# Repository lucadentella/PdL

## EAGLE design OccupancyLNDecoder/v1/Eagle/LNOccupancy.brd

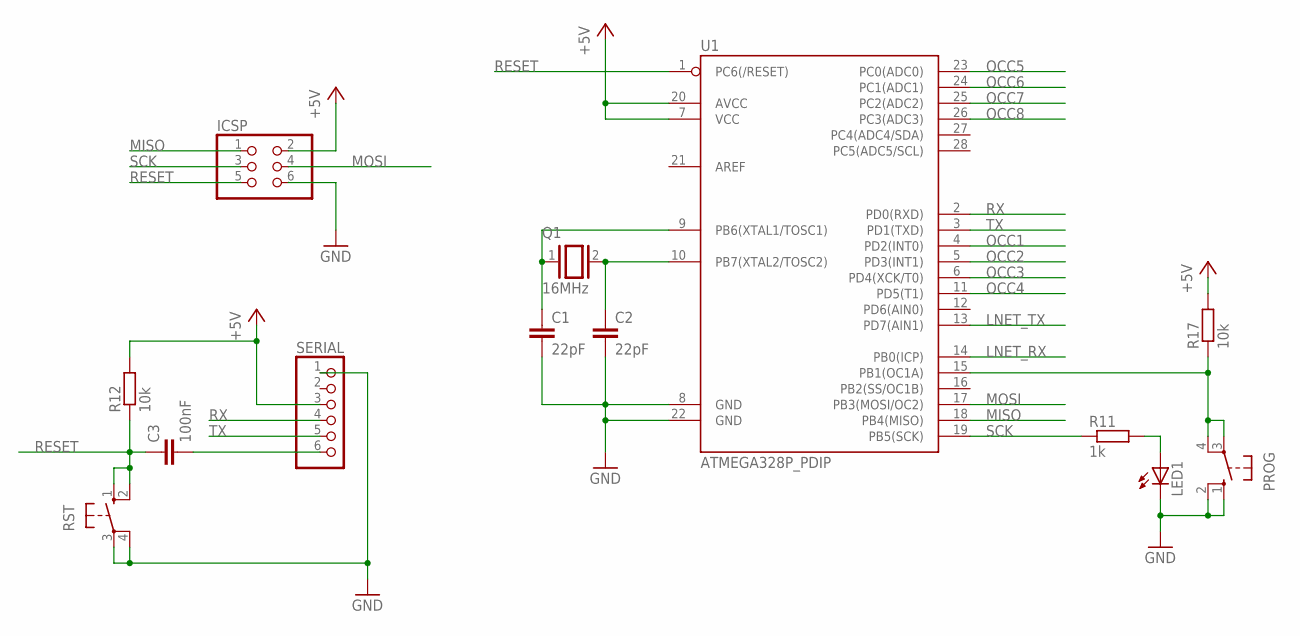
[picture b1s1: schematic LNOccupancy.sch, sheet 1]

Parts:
C1, C2: 22pF; C025-025X050
C3: 100nF; C050-025X075
ICSP: PINHD-2X3; 2X03
LED1: LED3MM
PROG: 10-XX; B3F-10XX
Q1: 16MHz; QS
R11: 1k; 0207/2V
R12, R17: 10k; 0207/2V
RST: 10-XX; B3F-10XX
SERIAL: PINHD-1X6; 1X06
U1: ATMEGA328P_PDIP; DIL28-3

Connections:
+5V: ICSP.2, R12.2, R17.2, SERIAL.3, U1.7 (VCC), U1.20 (AVCC); also elsewhere on the board
GND: C1.2, C2.2, ICSP.6, LED1.K (C), PROG.1 (S), PROG.2 (S1), RST.3, RST.4 (P1), SERIAL.1, U1.8 (GND), U1.22 (GND); also elsewhere on the board
LNET_RX: U1.14 (PB0(ICP)); also elsewhere on the board
LNET_TX: U1.13 (PD7(AIN1)); also elsewhere on the board
MISO: ICSP.1, U1.18 (PB4(MISO))
MOSI: ICSP.4, U1.17 (PB3(MOSI/OC2))
unnamed: C1.1, Q1.1, U1.9 (PB6(XTAL1/TOSC1))
unnamed: C2.1, Q1.2, U1.10 (PB7(XTAL2/TOSC2))
unnamed: LED1.A, R11.2
unnamed: C3.2, SERIAL.6
unnamed: PROG.3, PROG.4 (P1), R17.1, U1.15 (PB1(OC1A))
OCC1: U1.4 (PD2(INT0)); also elsewhere on the board
OCC2: U1.5 (PD3(INT1)); also elsewhere on the board
OCC3: U1.6 (PD4(XCK/T0)); also elsewhere on the board
OCC4: U1.11 (PD5(T1)); also elsewhere on the board
OCC5: U1.23 (PC0(ADC0)); also elsewhere on the board
OCC6: U1.24 (PC1(ADC1)); also elsewhere on the board
OCC7: U1.25 (PC2(ADC2)); also elsewhere on the board
OCC8: U1.26 (PC3(ADC3)); also elsewhere on the board
RESET: C3.1, ICSP.5, R12.1, RST.1 (S), RST.2 (S1), U1.1 (PC6(/RESET))
RX: SERIAL.4, U1.2 (PD0(RXD))
SCK: ICSP.3, R11.1, U1.19 (PB5(SCK))
TX: SERIAL.5, U1.3 (PD1(TXD))

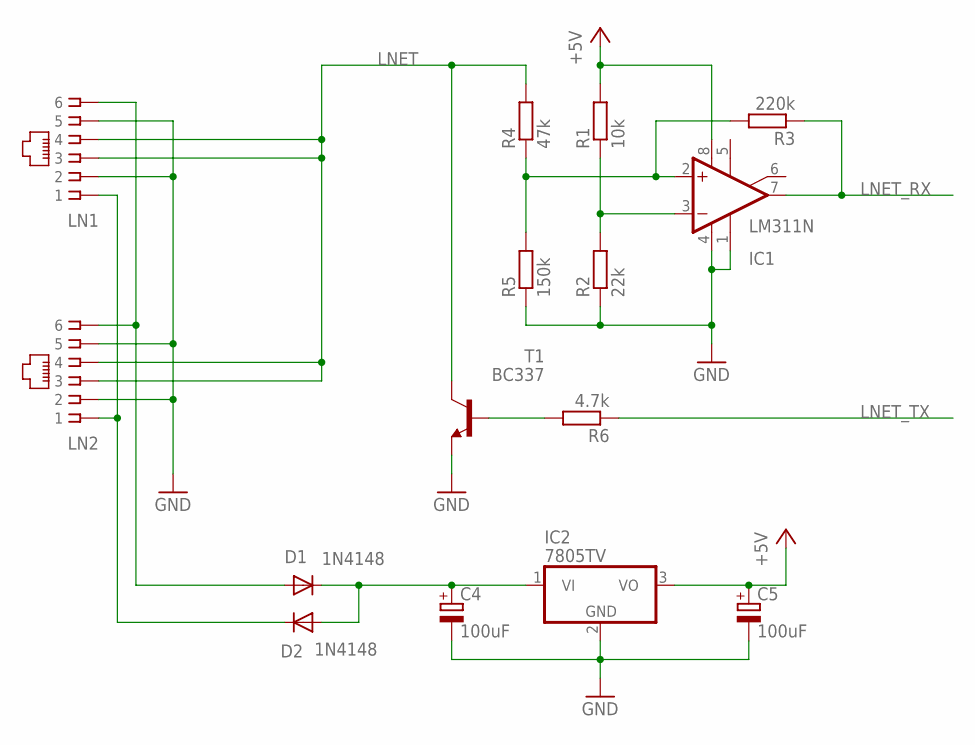
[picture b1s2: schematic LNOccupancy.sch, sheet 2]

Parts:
C4, C5: 100uF; E2,5-6
D1, D2: 1N4148; DO35-10
IC1: LM311N; DIL08
IC2: 7805TV; TO220V
LN1, LN2: RJ11-6X; RJ11-NO_SHIELD
R1: 10k; 0207/2V
R2: 22k; 0207/2V
R3: 220k; 0207/2V
R4: 47k; 0207/2V
R5: 150k; 0207/2V
R6: 4.7k; 0207/2V
T1: BC337; TO92

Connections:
+5V: C5.+, IC1.8 (V+), IC2.3 (VO), R1.2; also elsewhere on the board
GND: C4.-, C5.-, IC1.1 (GND), IC1.4 (V-), IC2.2 (GND), LN1.2, LN1.5, LN2.2, LN2.5, R2.1, R5.1, T1.1 (E); also elsewhere on the board
LNET: LN1.3, LN1.4, LN2.3, LN2.4, R4.2, T1.3 (C)
LNET_RX: IC1.7 (OUT), R3.1; also elsewhere on the board
LNET_TX: R6.1; also elsewhere on the board
unnamed: R6.2, T1.2 (B)
unnamed: IC1.3 (-IN), R1.1, R2.2
unnamed: IC1.2 (+IN), R3.2, R4.1, R5.2
unnamed: C4.+, D1.C, D2.A, IC2.1 (VI)
RAILSYNC_A: D1.A, LN1.6, LN2.6
RAILSYNC_B: D2.C, LN1.1, LN2.1

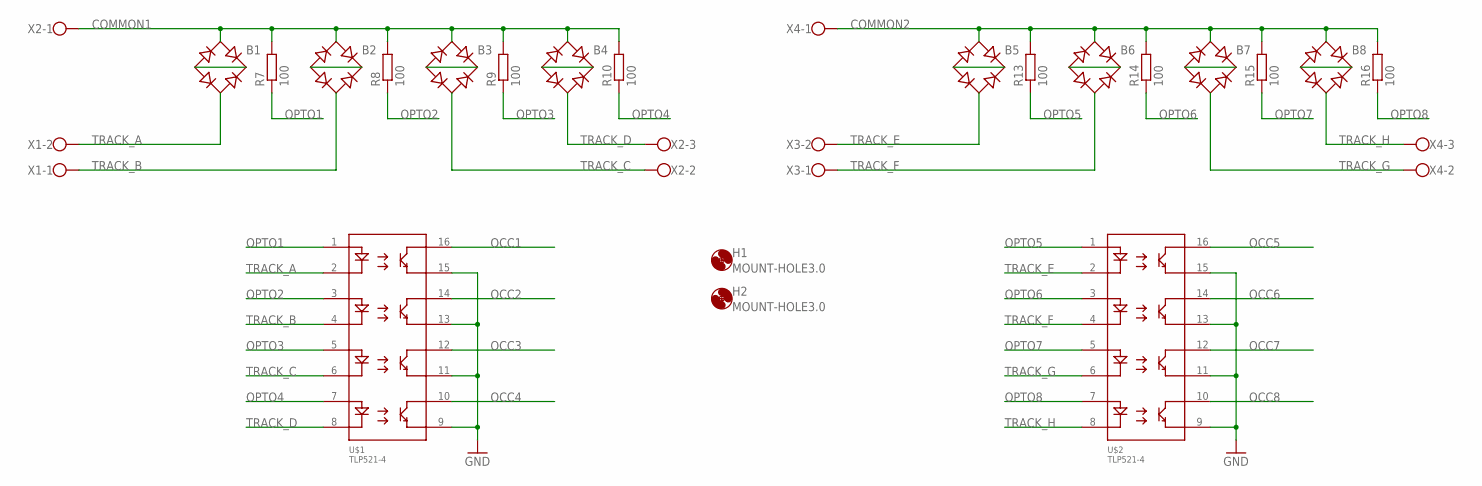
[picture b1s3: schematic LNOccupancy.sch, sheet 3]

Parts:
B1, B2, B3, B4, B5, B6, B7, B8: RB1A
H1, H2: MOUNT-HOLE3.0; 3,0
R7, R8, R9, R10, R13, R14, R15, R16: 100; 0207/2V
U$1, U$2: TLP521-4; DIL16
X1, X3: W237-102
X2, X4: W237-103

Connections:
COMMON1: B1.AC1, B2.AC1, B3.AC1, B4.AC1, R7.2, R8.2, R9.2, R10.2, X2.1
COMMON2: B5.AC1, B6.AC1, B7.AC1, B8.AC1, R13.2, R14.2, R15.2, R16.2, X4.1
GND: U$1.9, U$1.11, U$1.13, U$1.15, U$2.9, U$2.11, U$2.13, U$2.15; also elsewhere on the board
unnamed: B1.+, B1.-
unnamed: B3.+, B3.-
unnamed: B4.+, B4.-
unnamed: B2.+, B2.-
unnamed: B5.+, B5.-
unnamed: B6.+, B6.-
unnamed: B7.+, B7.-
unnamed: B8.+, B8.-
OCC1: U$1.16; also elsewhere on the board
OCC2: U$1.14; also elsewhere on the board
OCC3: U$1.12; also elsewhere on the board
OCC4: U$1.10; also elsewhere on the board
OCC5: U$2.16; also elsewhere on the board
OCC6: U$2.14; also elsewhere on the board
OCC7: U$2.12; also elsewhere on the board
OCC8: U$2.10; also elsewhere on the board
OPTO1: R7.1, U$1.1
OPTO2: R8.1, U$1.3
OPTO3: R9.1, U$1.5
OPTO4: R10.1, U$1.7
OPTO5: R13.1, U$2.1
OPTO6: R14.1, U$2.3
OPTO7: R15.1, U$2.5
OPTO8: R16.1, U$2.7
TRACK_A: B1.AC2, U$1.2, X1.2
TRACK_B: B2.AC2, U$1.4, X1.1
TRACK_C: B3.AC2, U$1.6, X2.2
TRACK_D: B4.AC2, U$1.8, X2.3
TRACK_E: B5.AC2, U$2.2, X3.2
TRACK_F: B6.AC2, U$2.4, X3.1
TRACK_G: B7.AC2, U$2.6, X4.2
TRACK_H: B8.AC2, U$2.8, X4.3

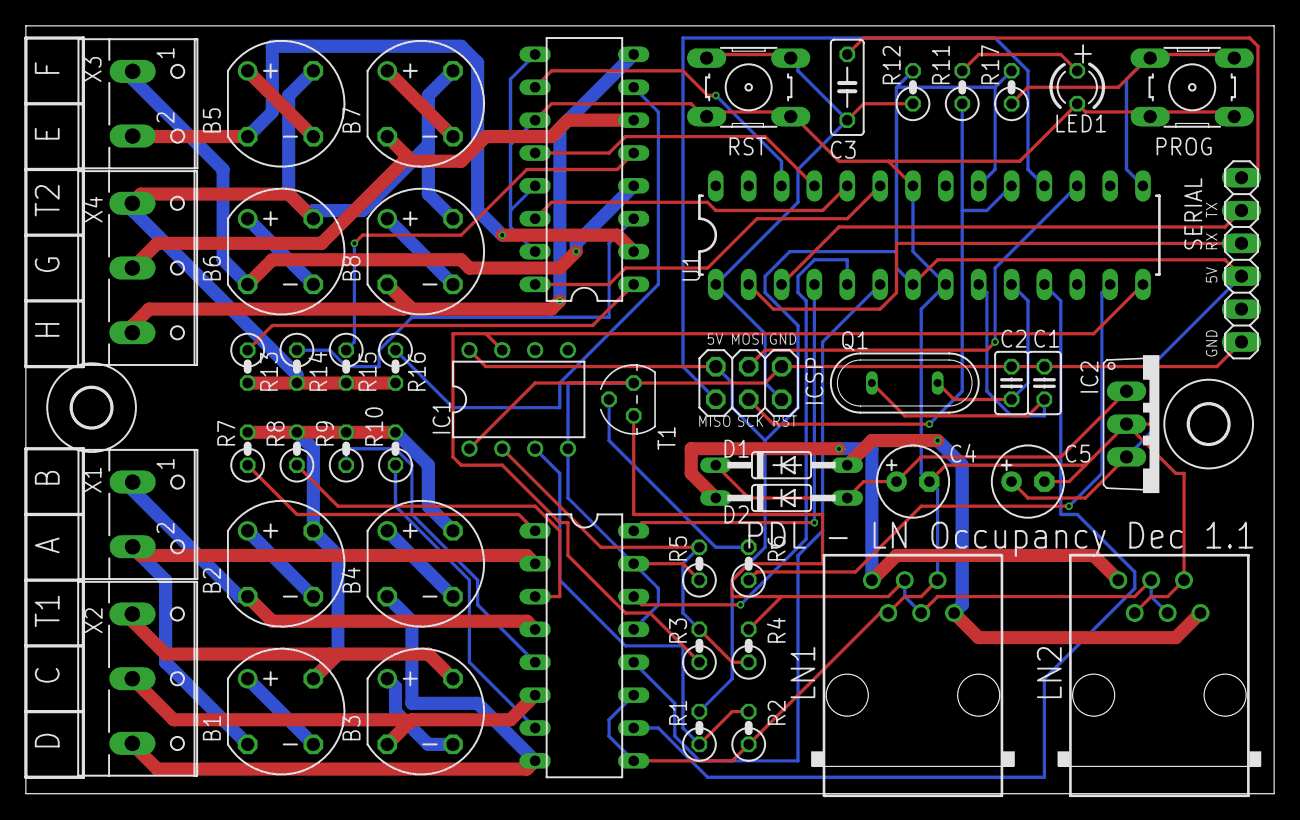
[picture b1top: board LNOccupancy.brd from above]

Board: 2 copper layers, 96.5 x 59.3 mm, 52 parts (0 on the bottom side), 56 nets.

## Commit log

2016-12-05 Initial commit for v2 firmware

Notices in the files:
parts and their libraries:
SparkFun-DigitalIC: Licensing: Creative Commons ShareAlike 4.0 International - https://creativecommons.org/licenses/by-sa/4.0
